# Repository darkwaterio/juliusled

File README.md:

#Julius ROV LED Array#

This is the repository for the PCB files for the Julius ROV LED Array. They are in Eagle PCB v7.0 format. I have also included the Gerber files for [Ragworm](http://ragworm.eu/) and [OSH Park](https://oshpark.com/).

As well as the PCB you will need the following:

* 1 x 3 pin header
* 1 x Mosfet IRL540N or similar logic level Mosfet
* 1 x 10K 0805 resistor
* 1 x 1K 0805 resistor
* 7 x 100R 0805 resistors (or whatever you have calculated for the LEDs you are using)
* 7 x 5mm LEDs - I used these https://www.sparkfun.com/products/531

Solder the resistors first, then the LEDs then the other components - it makes things simpler :)

##How they look##

##Powered and lit with blue LEDs##

I made one board up with [blue LEDs](https://www.sparkfun.com/products/529) - this is what it looks like powered up and on a low power level.

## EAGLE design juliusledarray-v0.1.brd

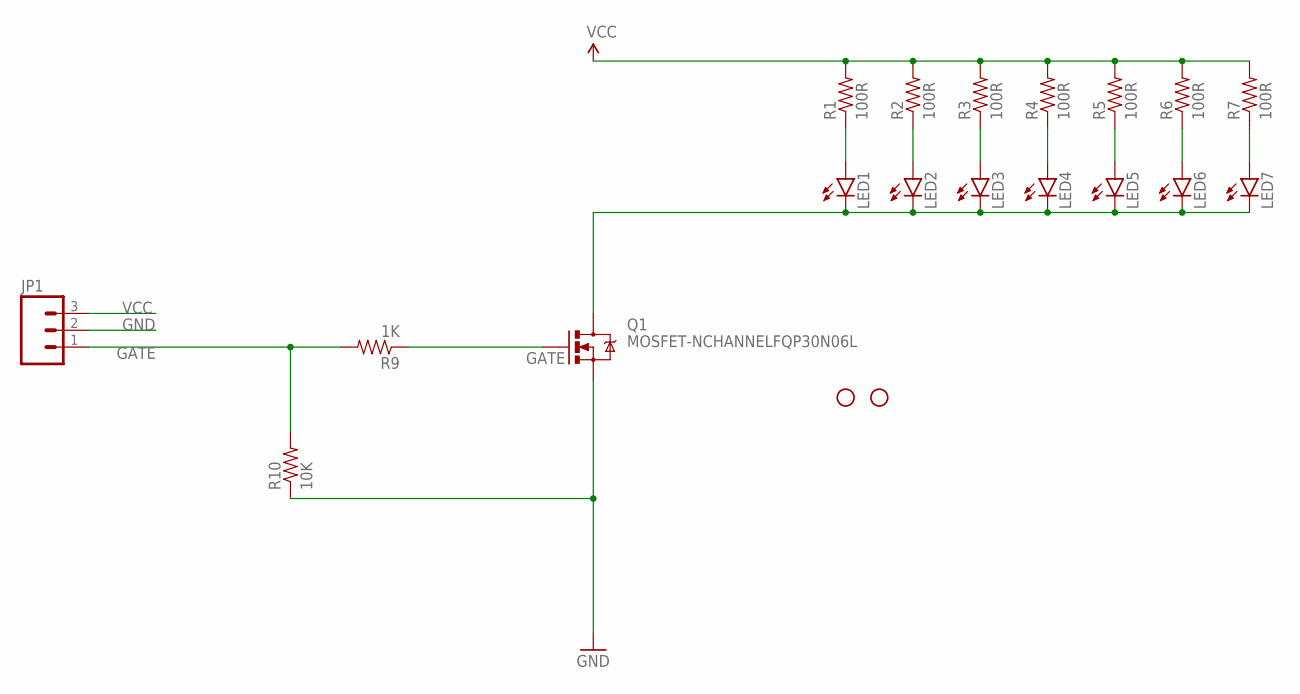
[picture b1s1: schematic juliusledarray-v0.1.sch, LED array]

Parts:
JP1: M03LOCK_LONGPADS; 1X03_LOCK_LONGPADS
LED1, LED2, LED3, LED4, LED5, LED6, LED7: LED5MM
Q1: MOSFET-NCHANNELFQP30N06L; TO220V
R1, R2, R3, R4, R5, R6, R7: 100R; 0805
R9: 1K; 0805
R10: 10K; 0805
STANDOFF1, STANDOFF2: STAND-OFF

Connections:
GATE: JP1.1, R9.2, R10.2
GND: JP1.2, Q1.3 (S), R10.1
unnamed: LED1.A, R1.1
unnamed: LED2.A, R2.1
unnamed: LED3.A, R3.1
unnamed: LED4.A, R4.1
unnamed: Q1.1 (G), R9.1
unnamed: LED5.A, R5.1
unnamed: LED6.A, R6.1
unnamed: LED7.A, R7.1
unnamed: LED1.K (C), LED2.K (C), LED3.K (C), LED4.K (C), LED5.K (C), LED6.K (C), LED7.K (C), Q1.2 (D)
VCC: JP1.3, R1.2, R2.2, R3.2, R4.2, R5.2, R6.2, R7.2

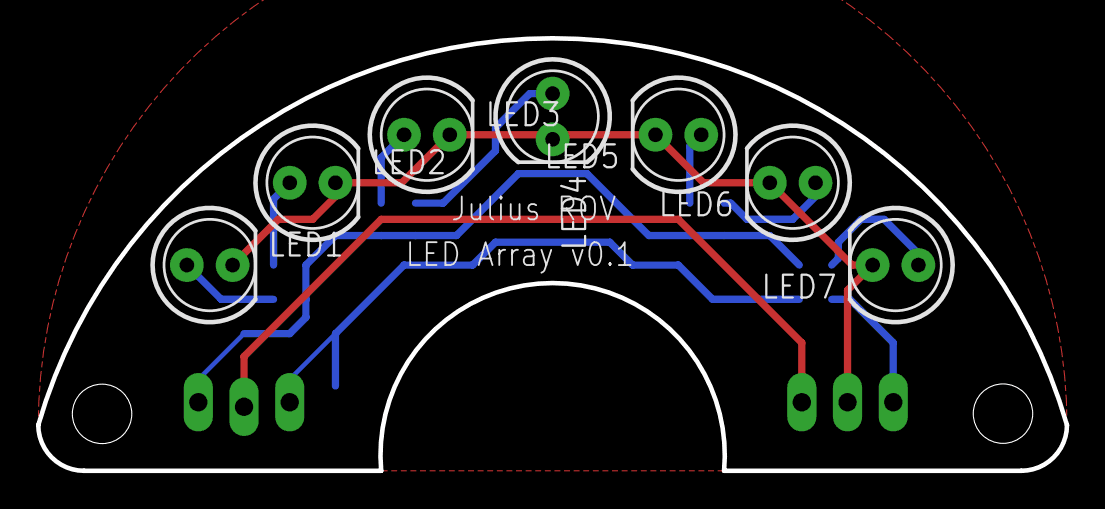
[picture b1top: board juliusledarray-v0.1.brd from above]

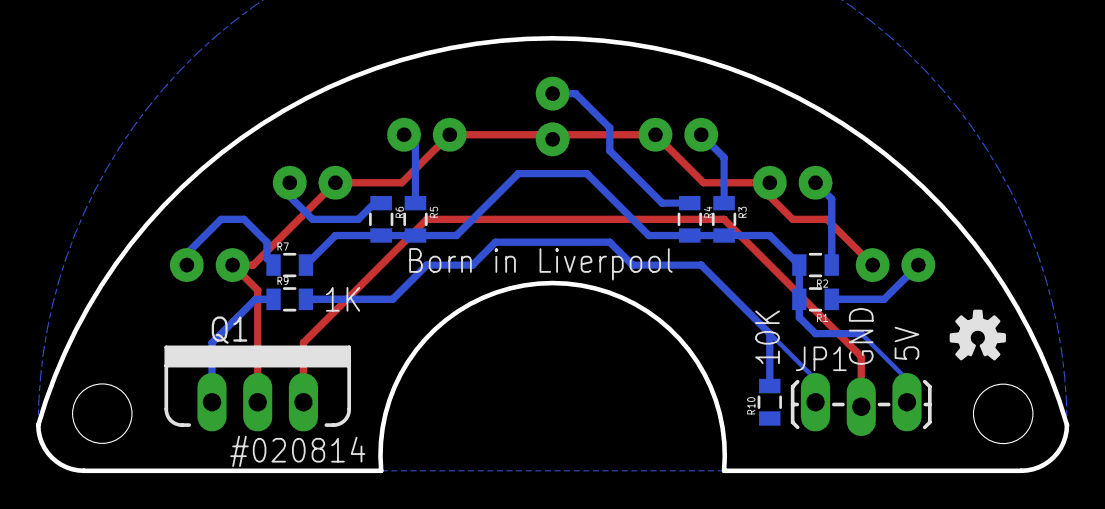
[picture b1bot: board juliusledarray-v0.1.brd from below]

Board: 2 copper layers, 57.1 x 24.0 mm, 21 parts (12 on the bottom side), 12 nets.

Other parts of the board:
U$1: OSHW-LOGO-S

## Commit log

2014-09-14 Initial commit of the LED array
2014-09-14 updated description and added images
2014-09-15 Added extra image

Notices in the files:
parts and their libraries:
SparkFun-LED: Licensing: Creative Commons ShareAlike 4.0 International - https://creativecommons.org/licenses/by-sa/4.0
